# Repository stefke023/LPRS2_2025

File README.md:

# LPRS2_2025

Tabela:
https://docs.google.com/spreadsheets/d/1wDiMKZ9upV2s28W13tgt96msm9oneCjL

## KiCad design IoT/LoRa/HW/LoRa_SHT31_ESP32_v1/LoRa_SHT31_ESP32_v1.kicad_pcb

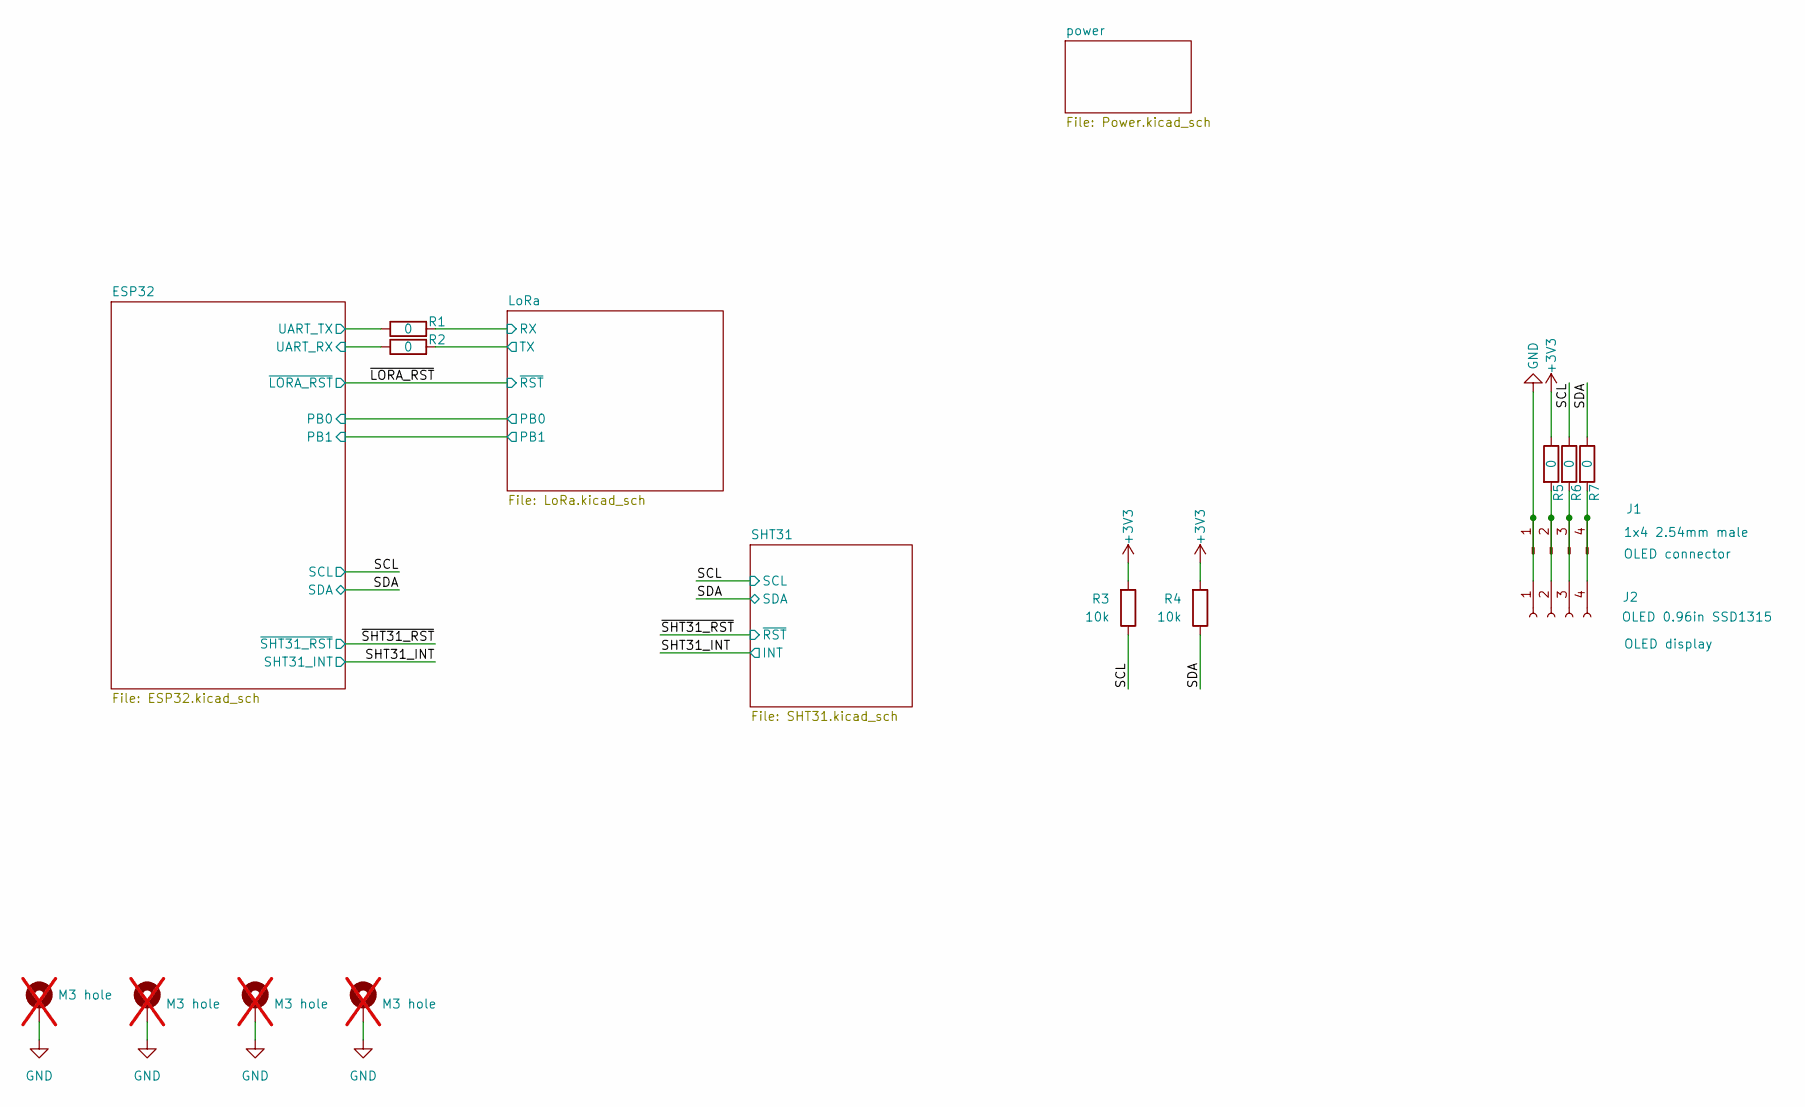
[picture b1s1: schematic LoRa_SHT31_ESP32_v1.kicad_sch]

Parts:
H1, H2, H3, H4: M3 hole; MountingHole_3.2mm_M3_Pad; not fitted
J1: 1x4 2.54mm male; HDR-TH_4P-P2.54-V-M; MFR.Part # B-2100S04P-A110; JLCPCB Part # C124378
J2: OLED 0.96in SSD1315; OLED-TH_L27.8-W27.2-P2.54_C9900033791; MFR.Part # HS96L03W2C03; JLCPCB Part # C5248080
R1, R2, R5, R6, R7: 0; R_0805_2012Metric; MFR.Part # 0805W8F0000T5E; JLCPCB Part # C17477
R3, R4: 10k; R_0805_2012Metric; MFR.Part # RC0805FR-0710KL; JLCPCB Part # C84376

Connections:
+3V3: R3.2, R4.2, R5.1; also elsewhere on the board
/ESP32/UART_RX: R2.1; also elsewhere on the board
/ESP32/UART_TX: R1.1; also elsewhere on the board
/LoRa/RX: R1.2; also elsewhere on the board
/LoRa/TX: R2.2; also elsewhere on the board
/SCL: R3.1, R6.1; also elsewhere on the board
/SDA: R4.1, R7.1; also elsewhere on the board
GND: H1.1, H2.1, H3.1, H4.1, J1.1, J2.1; also elsewhere on the board
unnamed: J1.2, J2.2, R5.2
unnamed: J1.3, J2.3, R6.2
unnamed: J1.4, J2.4, R7.2

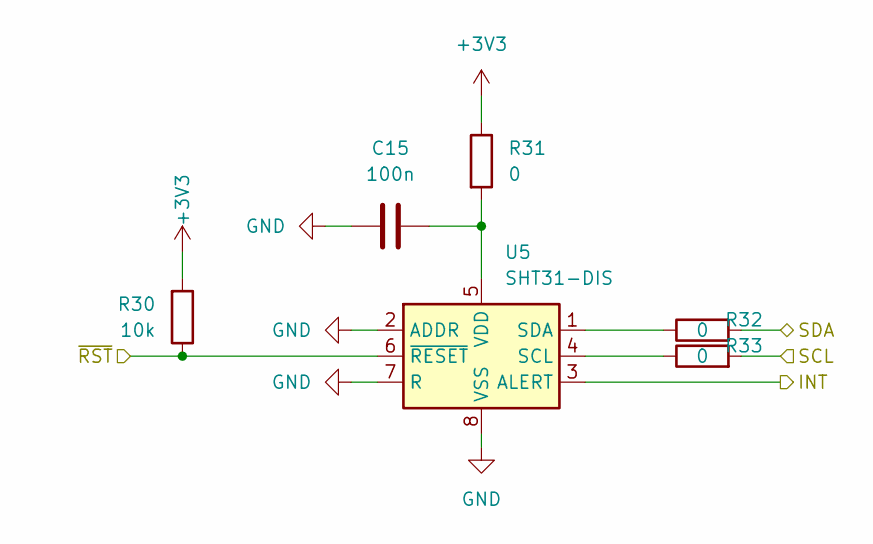
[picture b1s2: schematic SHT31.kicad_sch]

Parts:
C15: 100n; C_0805_2012Metric; MFR.Part # 0805B104J500NT; JLCPCB Part # C29926
R30: 10k; R_0805_2012Metric; MFR.Part # RC0805FR-0710KL; JLCPCB Part # C84376
R31, R32, R33: 0; R_0805_2012Metric; MFR.Part # 0805W8F0000T5E; JLCPCB Part # C17477
U5: SHT31-DIS; Sensirion_DFN-8-1EP_2.5x2.5mm_P0.5mm_EP1.1x1.7mm; MFR.Part # SHT31-DIS-B2.5kS; JLCPCB Part # C80862

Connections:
+3V3: R30.2, R31.1; also elsewhere on the board
/SCL: R33.2; also elsewhere on the board
/SDA: R32.2; also elsewhere on the board
/SHT31_INT: U5.3 (ALERT); also elsewhere on the board
/~SHT31_RST: R30.1, U5.6 (~RESET); also elsewhere on the board
GND: C15.1, U5.2 (ADDR), U5.7 (R), U5.8 (VSS), U5.9 (VSS); also elsewhere on the board
unnamed: R33.1, U5.4 (SCL)
unnamed: R32.1, U5.1 (SDA)
unnamed: C15.2, R31.2, U5.5 (VDD)

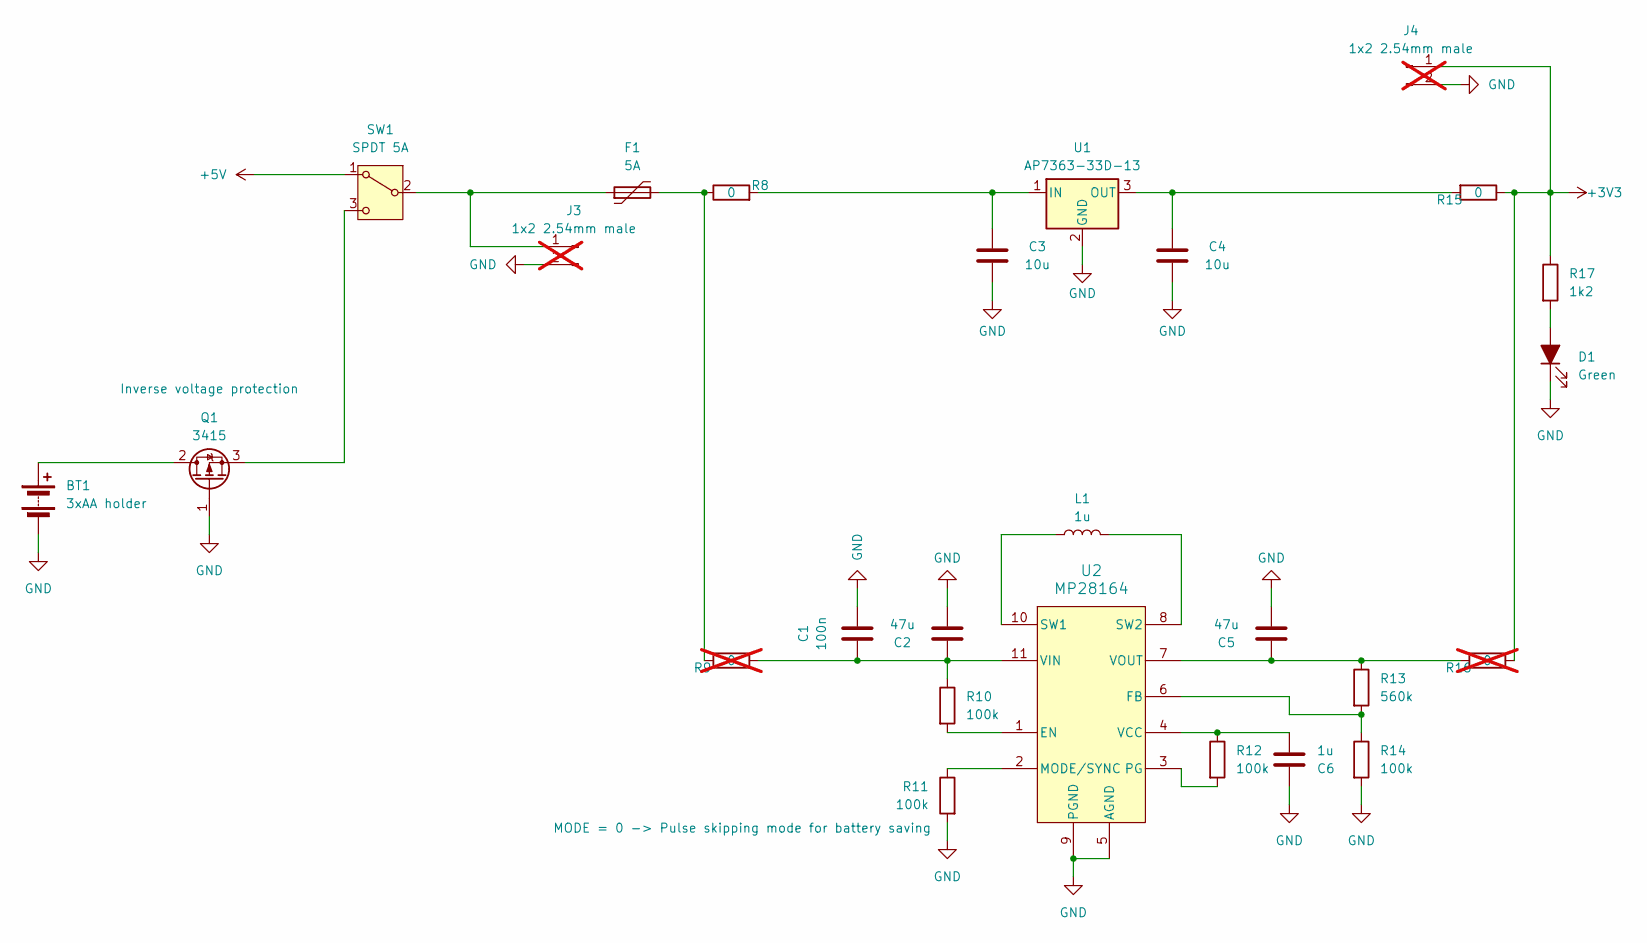
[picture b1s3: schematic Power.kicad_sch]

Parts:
BT1: 3xAA holder; BAT-TH_BH-AA-A1AJ029; MFR.Part # BH-AA-A1AJ029; JLCPCB Part # C7525429
C1: 100n; C_0805_2012Metric; MFR.Part # 0805B104J500NT; JLCPCB Part # C29926
C2, C5: 47u; C_0805_2012Metric; MFR.Part # CL21A476MQYNNNE; JLCPCB Part # C16780
C3, C4: 10u; C_0805_2012Metric; MFR.Part # CL21A106KAYNNNE; JLCPCB Part # C15850
C6: 1u; C_0805_2012Metric; MFR.Part # CL21B105KOFNNNE; JLCPCB Part # C24123
D1: Green; LED_0805_2012Metric_Pad1.15x1.40mm_HandSolder; MFR.Part # APT2012CGCK; JLCPCB Part # C5875740
F1: 5A; Fuse_2920_7451Metric; MFR.Part # SMD250L-30V; JLCPCB Part # C2937112
J3, J4: 1x2 2.54mm male; PinHeader_1x02_P2.54mm_Vertical; not fitted
L1: 1u; L_0805_2012Metric; MFR.Part # MCL2012S1R0MT; JLCPCB Part # C98325
Q1: 3415; SOT-23; MFR.Part # 3415; JLCPCB Part # C7431444
R8, R15: 0; R_0805_2012Metric; MFR.Part # 0805W8F0000T5E; JLCPCB Part # C17477
R9, R16: 0; R_0805_2012Metric; MFR.Part # 0805W8F0000T5E; JLCPCB Part # C17477; not fitted
R10, R11, R12, R14: 100k; R_0805_2012Metric; MFR.Part # RC0805FR-07100KL; JLCPCB Part # C96346
R13: 560k; R_0805_2012Metric; MFR.Part # 0805W8F5603T5E; JLCPCB Part # C15785
R17: 1k2; R_0805_2012Metric; MFR.Part # 0805W8F1201T5E; JLCPCB Part # C17379
SW1: SPDT 5A; SW-TH_K3-1391B-51; MFR.Part # K3-1391B-51; JLCPCB Part # C92656
U1: AP7363-33D-13; DPAK-3_L6.6-W6.1-P2.28-LS9.9-BR; MFR.Part # AP7363-33D-13; JLCPCB Part # C108723
U2: MP28164; QFN-11_MP28164_MNP; MFR.Part # MP28164GD-Z; JLCPCB Part # C114134

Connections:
+3V3: J4.1, R15.1, R16.1, R17.1; also elsewhere on the board
+5V: SW1.1 (A); also elsewhere on the board
GND: BT1.2 (-), C1.1, C2.1, C3.1, C4.1, C5.1, C6.1, D1.1 (K), J3.2, J4.2, Q1.1 (G), R11.2, R14.2, U1.2 (GND), U2.5 (AGND), U2.9 (PGND); also elsewhere on the board
unnamed: BT1.1 (+), Q1.2 (D)
unnamed: D1.2 (A), R17.2
unnamed: F1.2, R8.1, R9.2
unnamed: F1.1, J3.1, SW1.2 (B)
unnamed: Q1.3 (S), SW1.3 (C)
unnamed: C3.2, R8.2, U1.1 (IN)
unnamed: C4.2, R15.2, U1.3 (OUT)
unnamed: R10.2, U2.1 (EN)
unnamed: R13.2, R14.1, U2.6 (FB)
unnamed: R11.1, U2.2 (MODE/SYNC)
unnamed: R12.2, U2.3 (PG)
unnamed: L1.1, U2.10 (SW1)
unnamed: L1.2, U2.8 (SW2)
unnamed: C6.2, R12.1, U2.4 (VCC)
unnamed: C1.2, C2.2, R9.1, R10.1, U2.11 (VIN)
unnamed: C5.2, R13.1, R16.2, U2.7 (VOUT)

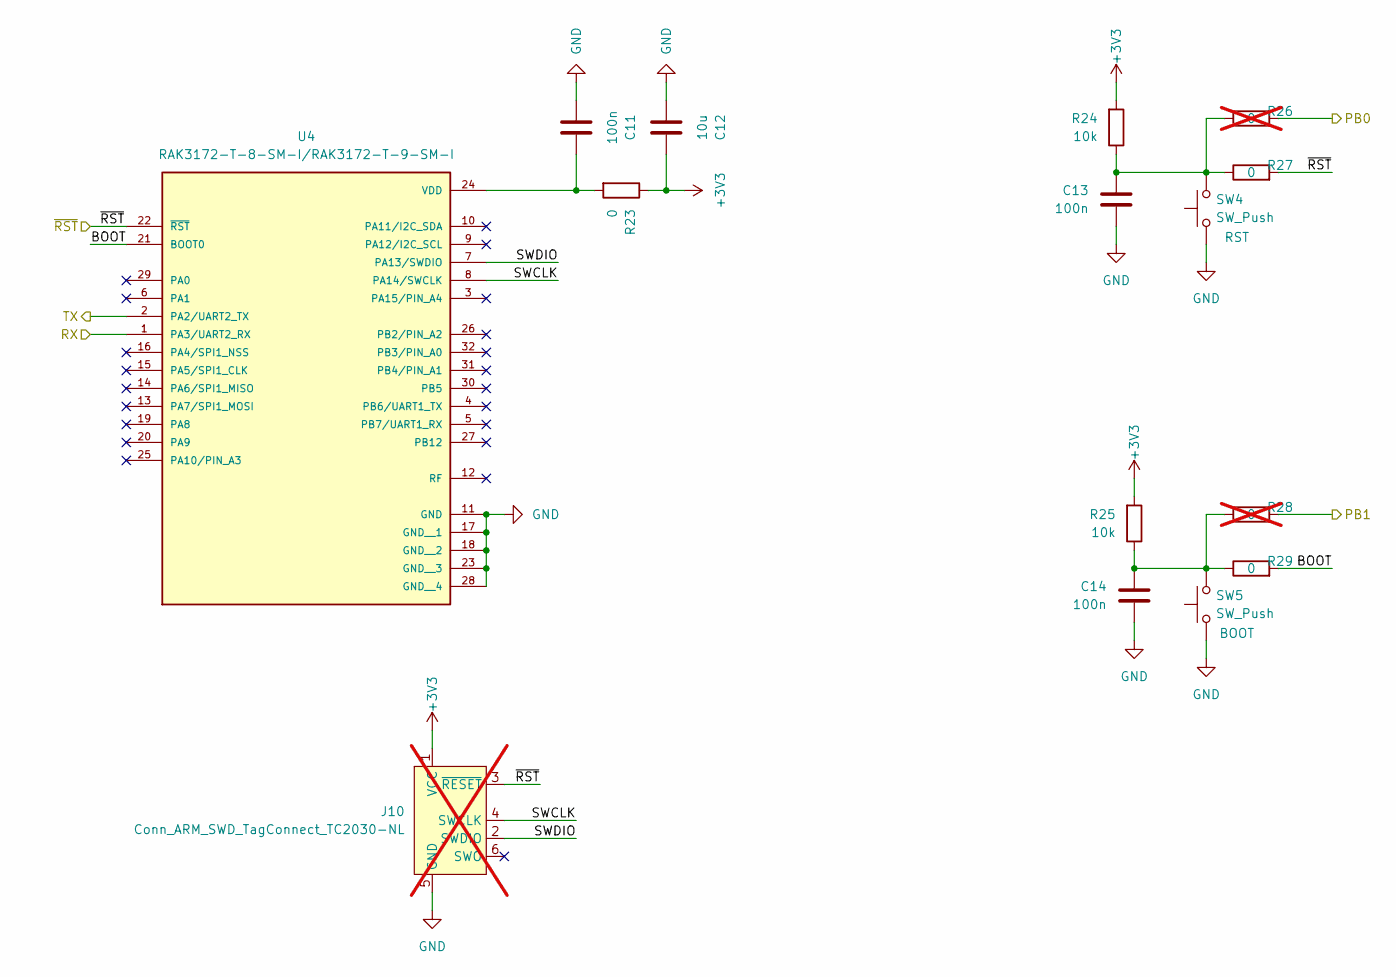
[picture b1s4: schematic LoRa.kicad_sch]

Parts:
C11, C13, C14: 100n; C_0805_2012Metric; MFR.Part # 0805B104J500NT; JLCPCB Part # C29926
C12: 10u; C_0805_2012Metric; MFR.Part # CL21A106KAYNNNE; JLCPCB Part # C15850
J10: Conn_ARM_SWD_TagConnect_TC2030-NL; Tag-Connect_TC2030-IDC-NL_2x03_P1.27mm_Vertical; not fitted
R23, R27, R29: 0; R_0805_2012Metric; MFR.Part # 0805W8F0000T5E; JLCPCB Part # C17477
R24, R25: 10k; R_0805_2012Metric; MFR.Part # RC0805FR-0710KL; JLCPCB Part # C84376
R26, R28: 0; R_0805_2012Metric; MFR.Part # 0805W8F0000T5E; JLCPCB Part # C17477; not fitted
SW4, SW5: SW_Push; SW-SMD_4P-L6.0-W6.0-P4.50-LS9.2; MFR.Part # TPS645-5NC60; JLCPCB Part # C19191552
U4: RAK3172-T-8-SM-I/RAK3172-T-9-SM-I; XCVR_RAK3172-8-SM-NI; PARTREV 4/11/2023; JLCPCB Part # C19723908

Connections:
+3V3: C12.2, J10.1 (VCC), R23.1, R24.2, R25.2; also elsewhere on the board
/ESP32/PB0: R26.2; also elsewhere on the board
/ESP32/SPARE_7: R28.2; also elsewhere on the board
/LoRa/BOOT: R29.2, U4.21 (BOOT0)
/LoRa/RX: U4.1 (PA3/UART2_RX); also elsewhere on the board
/LoRa/SWCLK: J10.4 (SWCLK), U4.8 (PA14/SWCLK)
/LoRa/SWDIO: J10.2 (SWDIO), U4.7 (PA13/SWDIO)
/LoRa/TX: U4.2 (PA2/UART2_TX); also elsewhere on the board
/~LORA_RST: J10.3 (~RESET), R27.2, U4.22 (~RST); also elsewhere on the board
GND: C11.1, C12.1, C13.1, C14.1, J10.5 (GND), SW4.1, SW5.1, U4.11 (GND), U4.17 (GND__1), U4.18 (GND__2), U4.23 (GND__3), U4.28 (GND__4); also elsewhere on the board
unnamed: C13.2, R24.1, R26.1, R27.1, SW4.2
unnamed: C14.2, R25.1, R28.1, R29.1, SW5.2
unnamed: C11.2, R23.2, U4.24 (VDD)

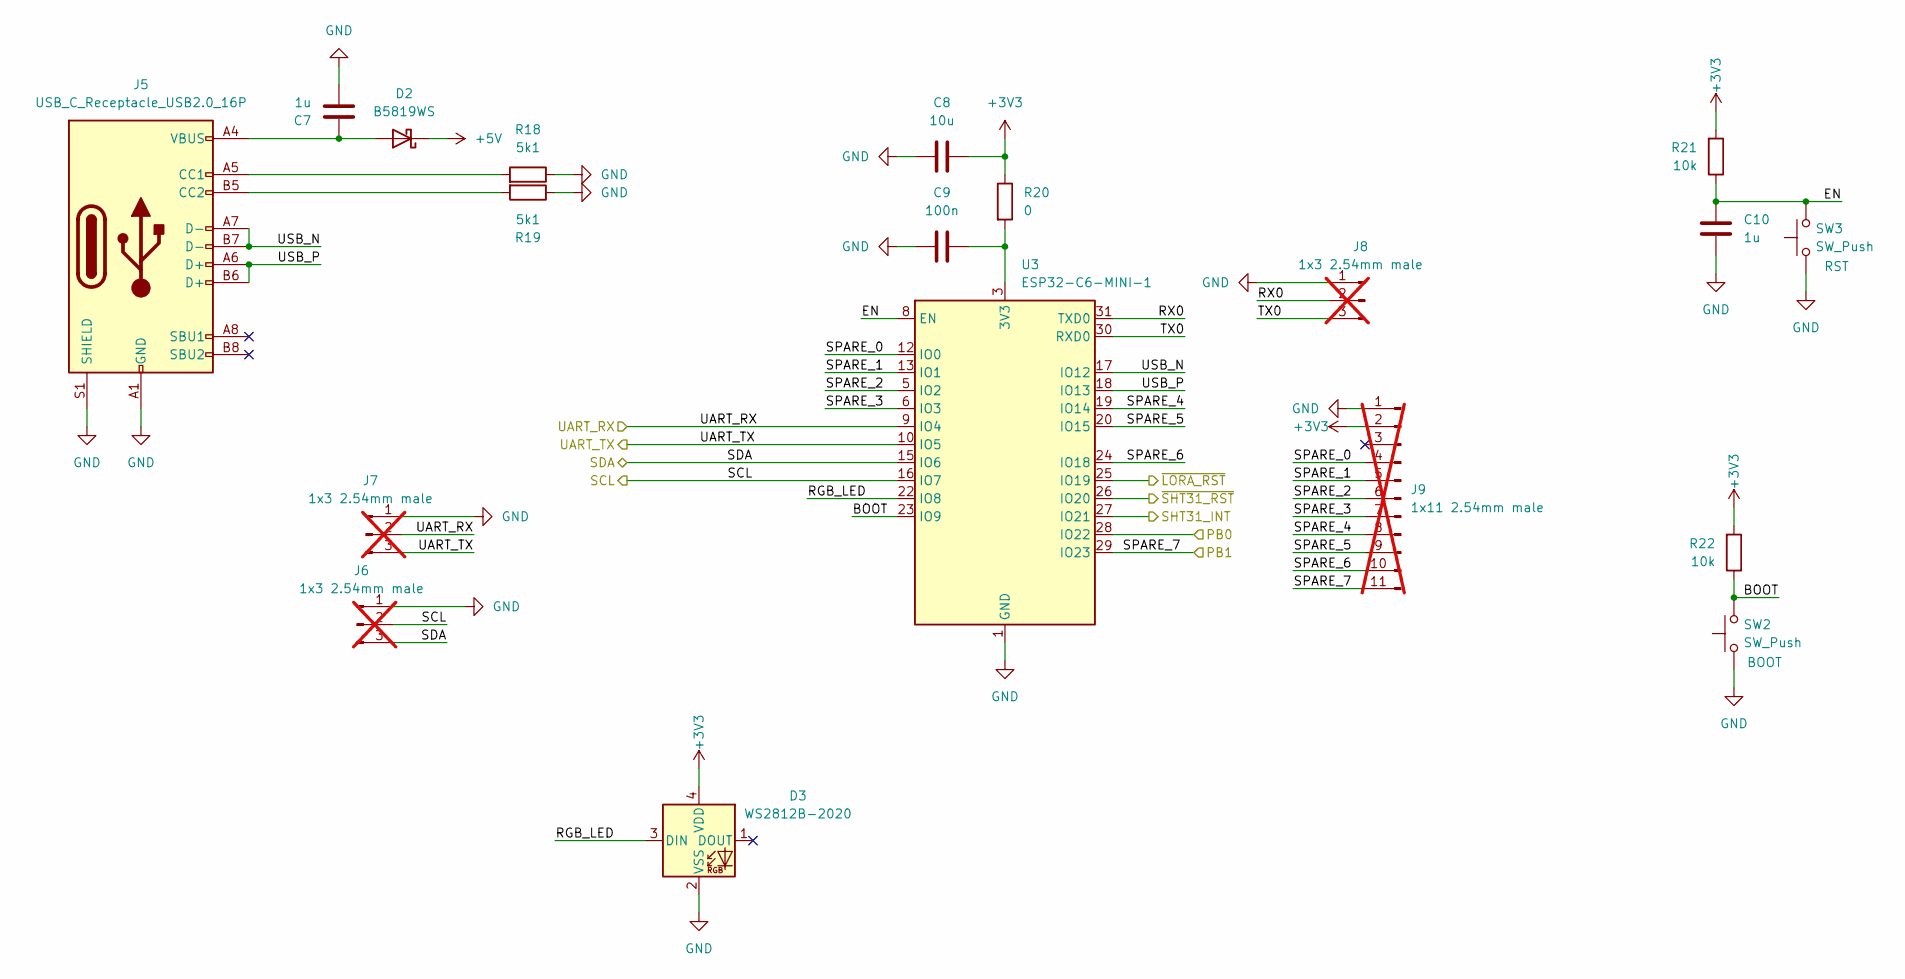
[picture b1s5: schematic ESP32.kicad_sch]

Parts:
C7, C10: 1u; C_0805_2012Metric; MFR.Part # CL21B105KOFNNNE; JLCPCB Part # C24123
C8: 10u; C_0805_2012Metric; MFR.Part # CL21A106KAYNNNE; JLCPCB Part # C15850
C9: 100n; C_0805_2012Metric; MFR.Part # 0805B104J500NT; JLCPCB Part # C29926
D2: B5819WS; D_SOD-323; MFR.Part # B5819WS; JLCPCB Part # C22624
D3: WS2812B-2020; LED_WS2812B-2020_PLCC4_2.0x2.0mm; MFR.Part # WS2812B-2020; JLCPCB Part # C965555
J5: USB_C_Receptacle_USB2.0_16P; USB_C_Receptacle_G-Switch_GT-USB-7010ASV; MFR.Part # TYPE-C16PIN; JLCPCB Part # C393939
J6, J7, J8: 1x3 2.54mm male; PinHeader_1x03_P2.54mm_Vertical; not fitted
J9: 1x11 2.54mm male; PinHeader_1x11_P2.54mm_Vertical; not fitted
R18, R19: 5k1; R_0805_2012Metric; MFR.Part # C27834; JLCPCB Part # C27834
R20: 0; R_0805_2012Metric; MFR.Part # 0805W8F0000T5E; JLCPCB Part # C17477
R21, R22: 10k; R_0805_2012Metric; MFR.Part # RC0805FR-0710KL; JLCPCB Part # C84376
SW2, SW3: SW_Push; SW-SMD_4P-L6.0-W6.0-P4.50-LS9.2; MFR.Part # TPS645-5NC60; JLCPCB Part # C19191552
U3: ESP32-C6-MINI-1; MFR.Part # ESP32-C6-MINI-1-N4; JLCPCB Part # C5736265

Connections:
+3V3: C8.2, D3.4 (VDD), J9.2, R20.1, R21.2, R22.2; also elsewhere on the board
+5V: D2.1 (K); also elsewhere on the board
/ESP32/BOOT: R22.1, SW2.2, U3.23 (IO9)
/ESP32/EN: C10.1, R21.1, SW3.2, U3.8 (EN)
/ESP32/PB0: U3.28 (IO22); also elsewhere on the board
/ESP32/RGB_LED: D3.3 (DIN), U3.22 (IO8)
/ESP32/RX0: J8.2, U3.31 (TXD0)
/ESP32/SPARE_0: J9.4, U3.12 (IO0)
/ESP32/SPARE_1: J9.5, U3.13 (IO1)
/ESP32/SPARE_2: J9.6, U3.5 (IO2)
/ESP32/SPARE_3: J9.7, U3.6 (IO3)
/ESP32/SPARE_4: J9.8, U3.19 (IO14)
/ESP32/SPARE_5: J9.9, U3.20 (IO15)
/ESP32/SPARE_6: J9.10, U3.24 (IO18)
/ESP32/SPARE_7: J9.11, U3.29 (IO23); also elsewhere on the board
/ESP32/TX0: J8.3, U3.30 (RXD0)
/ESP32/UART_RX: J7.2, U3.9 (IO4); also elsewhere on the board
/ESP32/UART_TX: J7.3, U3.10 (IO5); also elsewhere on the board
/ESP32/USB_N: J5.A7 (D-), J5.B7 (D-), U3.17 (IO12)
/ESP32/USB_P: J5.A6 (D+), J5.B6 (D+), U3.18 (IO13)
/SCL: J6.2, U3.16 (IO7); also elsewhere on the board
/SDA: J6.3, U3.15 (IO6); also elsewhere on the board
/SHT31_INT: U3.27 (IO21); also elsewhere on the board
/~LORA_RST: U3.25 (IO19); also elsewhere on the board
/~SHT31_RST: U3.26 (IO20); also elsewhere on the board
GND: C7.2, C8.1, C9.1, C10.2, D3.2 (VSS), J5.A1 (GND), J5.A12 (GND), J5.B1 (GND), J5.B12 (GND), J5.S1 (SHIELD), J6.1, J7.1, J8.1, J9.1, R18.1, R19.1, SW2.1, SW3.1, U3.1 (GND), U3.2 (GND), U3.11 (GND), U3.14 (GND), U3.36 (GND), U3.37 (GND), U3.38 (GND), U3.39 (GND), U3.40 (GND), U3.41 (GND), U3.42 (GND), U3.43 (GND), U3.44 (GND), U3.45 (GND), U3.46 (GND), U3.47 (GND), U3.48 (GND), U3.49 (GND), U3.50 (GND), U3.51 (GND), U3.52 (GND), U3.53 (GND); also elsewhere on the board
unnamed: C7.1, D2.2 (A), J5.A4 (VBUS), J5.A9 (VBUS), J5.B4 (VBUS), J5.B9 (VBUS)
unnamed: J5.A5 (CC1), R18.2
unnamed: J5.B5 (CC2), R19.2
unnamed: C9.2, R20.2, U3.3 (3V3)

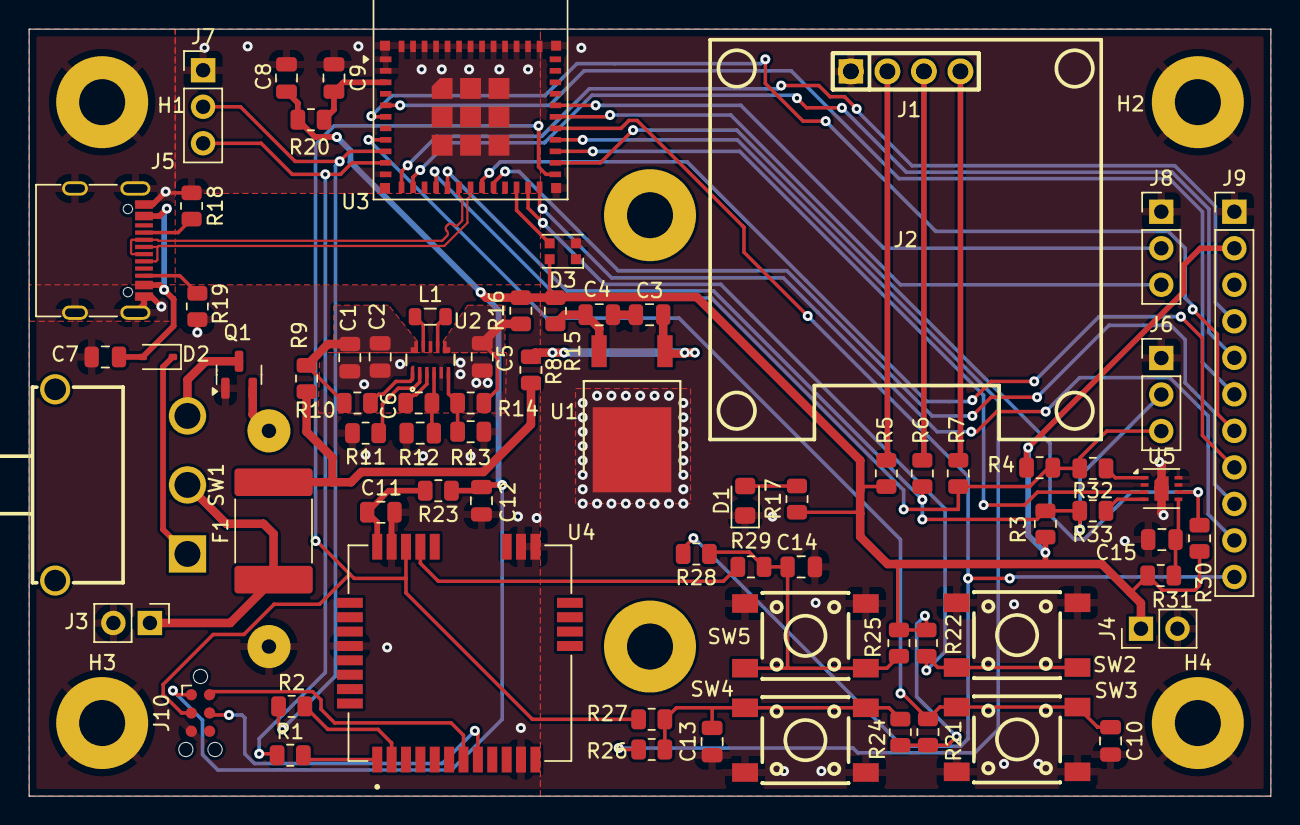
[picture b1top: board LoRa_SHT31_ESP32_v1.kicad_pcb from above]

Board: 4 copper layers, 86.4 x 53.3 mm, 79 parts (1 on the bottom side), 60 nets.

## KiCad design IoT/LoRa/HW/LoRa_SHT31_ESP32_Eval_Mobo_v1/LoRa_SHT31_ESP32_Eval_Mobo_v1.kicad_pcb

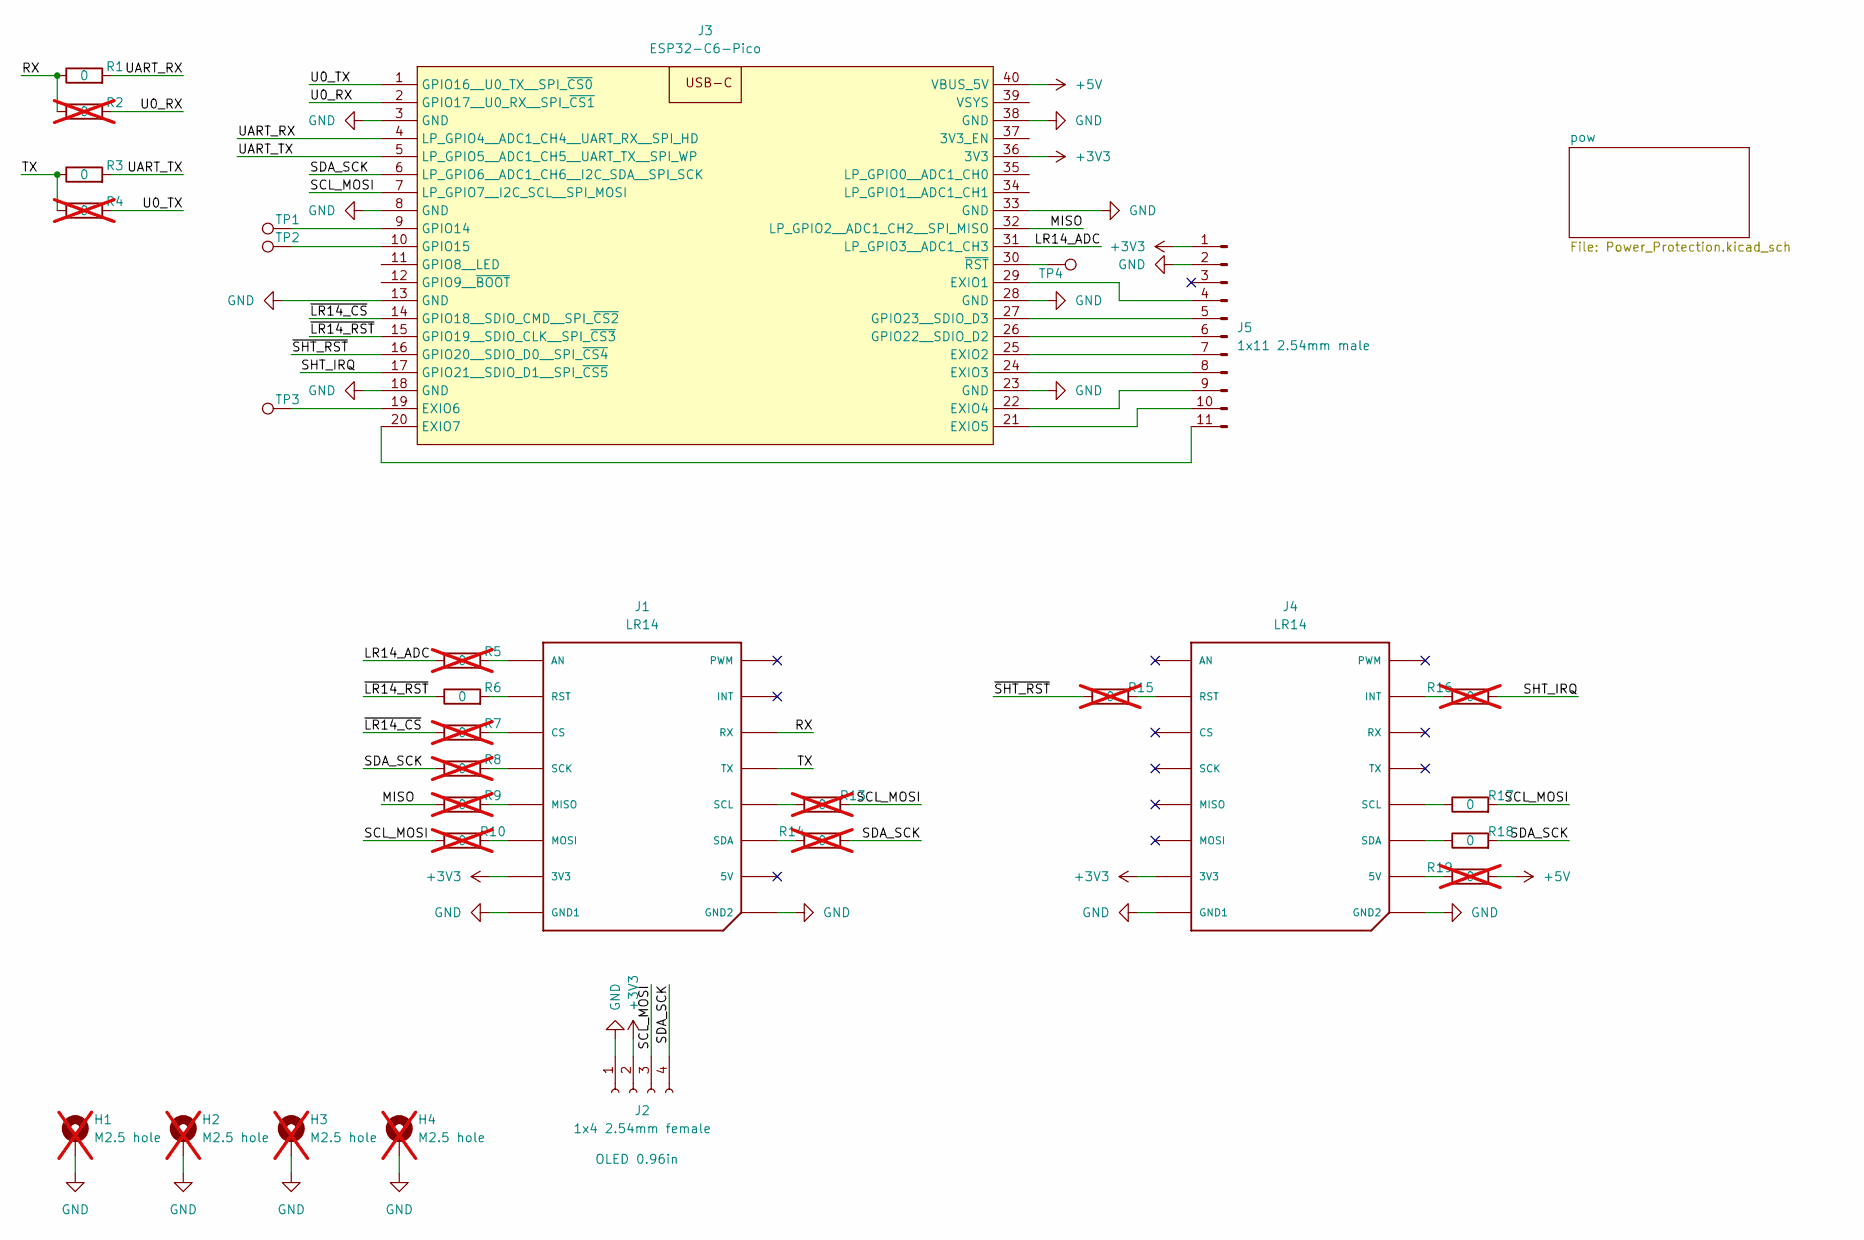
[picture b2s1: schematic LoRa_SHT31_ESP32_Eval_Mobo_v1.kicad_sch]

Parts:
H1, H2, H3, H4: M2.5 hole; MountingHole_2.7mm_M2.5_Pad; not fitted
J1, J4: LR14; MIKROBUS_HOST_CONN
J2: 1x4 2.54mm female; PinSocket_1x04_P2.54mm_Vertical
J3: ESP32-C6-Pico
J5: 1x11 2.54mm male; PinHeader_1x11_P2.54mm_Vertical
R1, R3, R6, R17, R18: 0; R_Axial_DIN0207_L6.3mm_D2.5mm_Pinf_Horizontal
R2, R4, R5, R7, R8, R9, R10, R13, R14, R15, R16, R19: 0; R_Axial_DIN0207_L6.3mm_D2.5mm_Pinf_Horizontal; not fitted
TP1, TP2, TP3, TP4: 1x1 2x54mm male; PinHeader_1x01_P2.54mm_Vertical

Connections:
+3V3: J1.P7 (3V3), J2.2, J3.36 (3V3), J4.P7 (3V3), J5.1
+5V: J3.40 (VBUS_5V), R19.1; also elsewhere on the board
/LR14_ADC: J3.31 (LP_GPIO3__ADC1_CH3), R5.1
/MISO: J3.32 (LP_GPIO2__ADC1_CH2__SPI_MISO), R9.1
/RX: J1.P14 (RX), R1.1, R2.1
/SCL_MOSI: J2.3, J3.7 (LP_GPIO7__I2C_SCL__SPI_MOSI), R10.1, R13.2, R17.2
/SDA_SCK: J2.4, J3.6 (LP_GPIO6__ADC1_CH6__I2C_SDA__SPI_SCK), R8.1, R14.1, R18.2
/SHT_IRQ: J3.17 (GPIO21__SDIO_D1__SPI_~CS5), R16.1
/TX: J1.P13 (TX), R3.1, R4.1
/U0_RX: J3.2 (GPIO17__U0_RX__SPI_~CS1), R2.2
/U0_TX: J3.1 (GPIO16__U0_TX__SPI_~CS0), R4.2
/UART_RX: J3.4 (LP_GPIO4__ADC1_CH4__UART_RX__SPI_HD), R1.2
/UART_TX: J3.5 (LP_GPIO5__ADC1_CH5__UART_TX__SPI_WP), R3.2
/~LR14_CS: J3.14 (GPIO18__SDIO_CMD__SPI_~CS2), R7.1
/~LR14_RST: J3.15 (GPIO19__SDIO_CLK__SPI_~CS3), R6.1
/~SHT_RST: J3.16 (GPIO20__SDIO_D0__SPI_~CS4), R15.1
GND: H1.1, H2.1, H3.1, H4.1, J1.P8 (GND1), J1.P9 (GND2), J2.1, J3.3 (GND), J3.8 (GND), J3.13 (GND), J3.18 (GND), J3.23 (GND), J3.28 (GND), J3.33 (GND), J3.38 (GND), J4.P8 (GND1), J4.P9 (GND2), J5.2; also elsewhere on the board
unnamed: J1.P1 (AN), R5.2
unnamed: J1.P3 (CS), R7.2
unnamed: J1.P5 (MISO), R9.2
unnamed: J1.P6 (MOSI), R10.2
unnamed: J1.P2 (RST), R6.2
unnamed: J1.P4 (SCK), R8.2
unnamed: J1.P12 (SCL), R13.1
unnamed: J1.P11 (SDA), R14.2
unnamed: J3.29 (EXIO1), J5.4
unnamed: J3.25 (EXIO2), J5.7
unnamed: J3.24 (EXIO3), J5.8
unnamed: J3.22 (EXIO4), J5.9
unnamed: J3.21 (EXIO5), J5.10
unnamed: J3.19 (EXIO6), TP3.1
unnamed: J3.20 (EXIO7), J5.11
unnamed: J3.9 (GPIO14), TP1.1
unnamed: J3.10 (GPIO15), TP2.1
unnamed: J3.26 (GPIO22__SDIO_D2), J5.6
unnamed: J3.27 (GPIO23__SDIO_D3), J5.5
unnamed: J3.30 (~RST), TP4.1
unnamed: J4.P10 (5V), R19.2
unnamed: J4.P15 (INT), R16.2
unnamed: J4.P2 (RST), R15.2
unnamed: J4.P12 (SCL), R17.1
unnamed: J4.P11 (SDA), R18.1

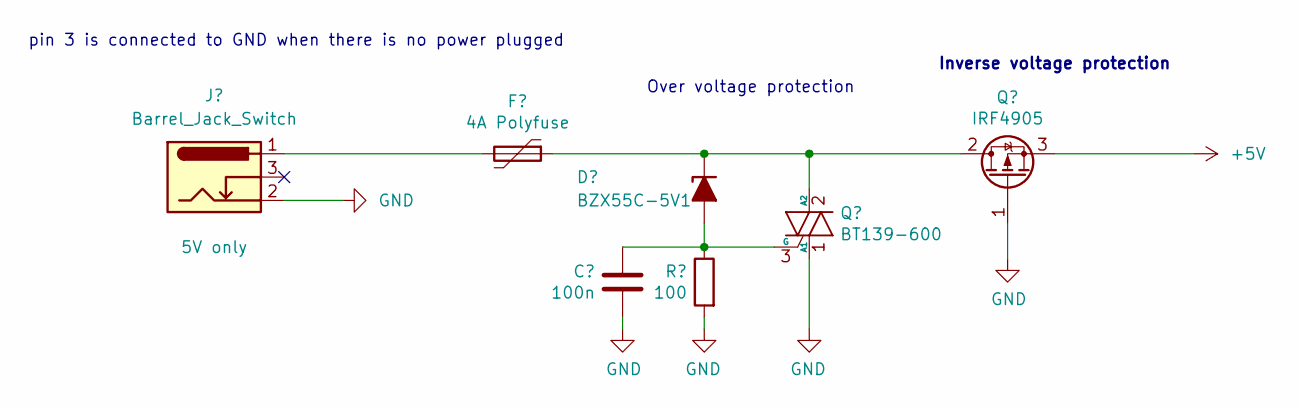
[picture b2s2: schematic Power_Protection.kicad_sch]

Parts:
C1: 100n; C_Disc_D3.0mm_W1.6mm_P5.00mm
D1: BZX55C-5V1; D_DO-35_SOD27_P2.54mm_Vertical_KathodeUp
F1: 4A Polyfuse; C_Disc_D3.0mm_W1.6mm_P5.00mm
J6: Barrel_Jack_Switch; BarrelJack_Horizontal
Q1: BT139-600; TO-220-3_Vertical
Q2: IRF4905; TO-220-3_Vertical
R20: 100; R_Axial_DIN0207_L6.3mm_D2.5mm_P10.16mm_Horizontal

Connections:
+5V: Q2.3 (S); also elsewhere on the board
GND: C1.1, J6.2, Q1.1 (A1), Q2.1 (G), R20.2; also elsewhere on the board
unnamed: C1.2, D1.2 (A), Q1.3 (G), R20.1
unnamed: D1.1 (K), F1.1, Q1.2 (A2), Q2.2 (D)
unnamed: F1.2, J6.1

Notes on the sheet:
Inverse voltage protection
pin 3 is connected to GND when there is no power plugged
Over voltage protection

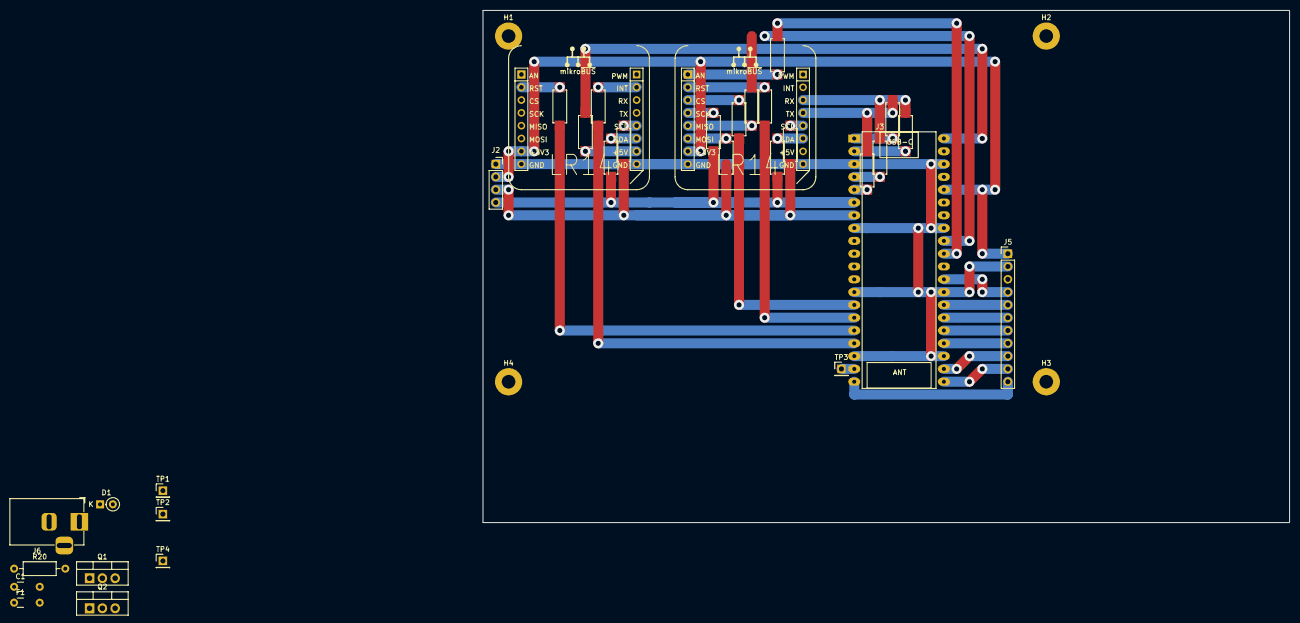
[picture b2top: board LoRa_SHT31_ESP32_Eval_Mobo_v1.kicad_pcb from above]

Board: 2 copper layers, 160.0 x 101.6 mm, 37 parts (0 on the bottom side), 45 nets.

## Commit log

2025-09-12 Initial commit.
2025-09-18 ESP32 LoRa.
2025-09-18 GPU.
2025-09-22 Link to tabela
2025-09-23 How to burn.
2025-10-22 Stefan Onc i Dusan Micic
2025-10-22 Finalna verzija projekta
